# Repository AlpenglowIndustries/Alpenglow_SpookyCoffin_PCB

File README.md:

# Alpenglow_SpookyCoffin_PCB
A Halloween-themed beginning soldering blinky board with self-flickering LEDs.

You can buy this kit on Tindie or our website
https://www.tindie.com/products/alpenglow/spooky-coffin/
https://www.alpenglowindustries.com/store/p11/Spooky_Coffin.html#/

Solder instructions on Hackaday:
https://hackaday.io/project/182264-spooky-coffin

Link to the art work by Gabriel VanHelsing under a Creative Commons CC-BY-SA-3.0 license
https://commons.wikimedia.org/wiki/File:Skull_%26_Crossbones_BW.png

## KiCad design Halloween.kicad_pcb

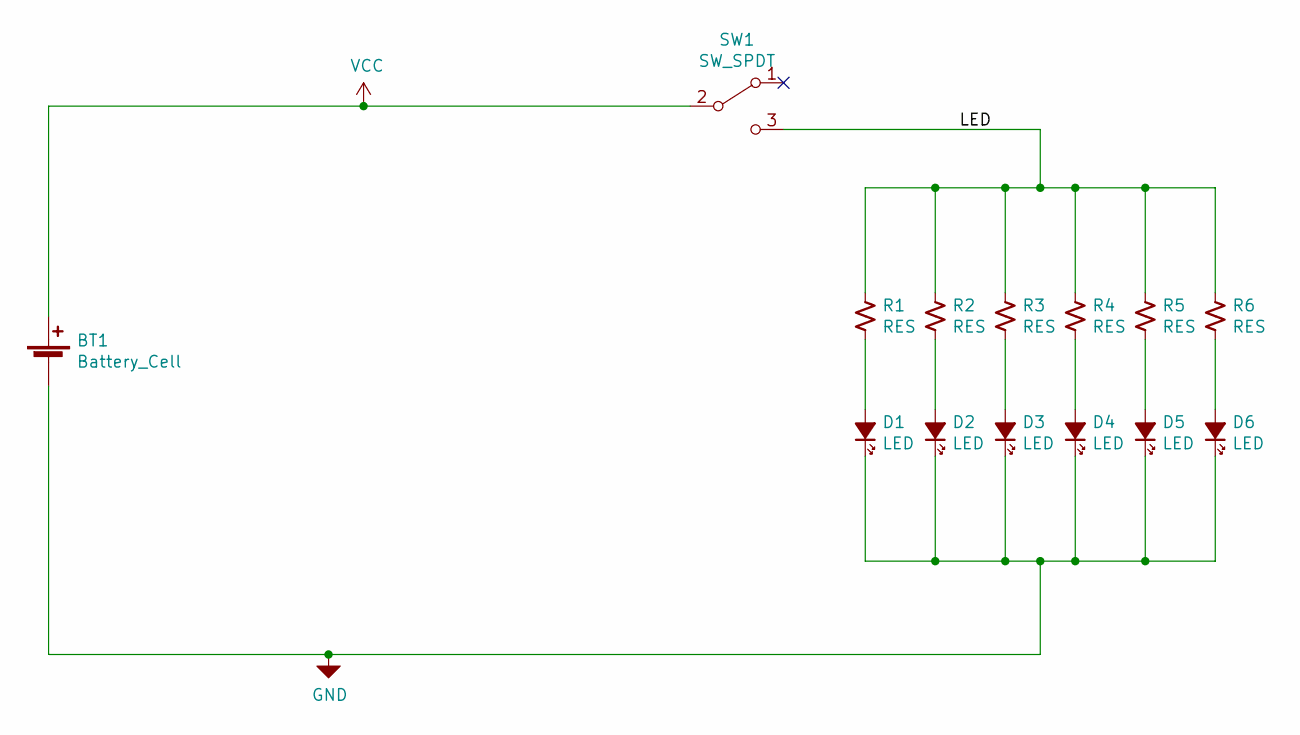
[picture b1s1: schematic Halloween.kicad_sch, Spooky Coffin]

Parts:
BT1: Battery_Cell; BatteryHolder_MPD_BK888_2032_THRU
D1, D2, D3, D4, D5, D6: LED; LED_D3.0mm
R1, R2, R3, R4, R5, R6: RES; R_Axial_DIN0207_L6.3mm_D2.5mm_P10.16mm_Horizontal
SW1: SW_SPDT; SW_SPDT_SLIDE_THRU_RTA

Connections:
/LED: R1.1, R2.1, R3.1, R4.1, R5.1, R6.1, SW1.3 (C)
GND: BT1.2 (-), D1.1 (K), D2.1 (K), D3.1 (K), D4.1 (K), D5.1 (K), D6.1 (K)
unnamed: D1.2 (A), R1.2
unnamed: D2.2 (A), R2.2
unnamed: D3.2 (A), R3.2
unnamed: D4.2 (A), R4.2
unnamed: D5.2 (A), R5.2
unnamed: D6.2 (A), R6.2
VCC: BT1.1 (+), SW1.2 (B)

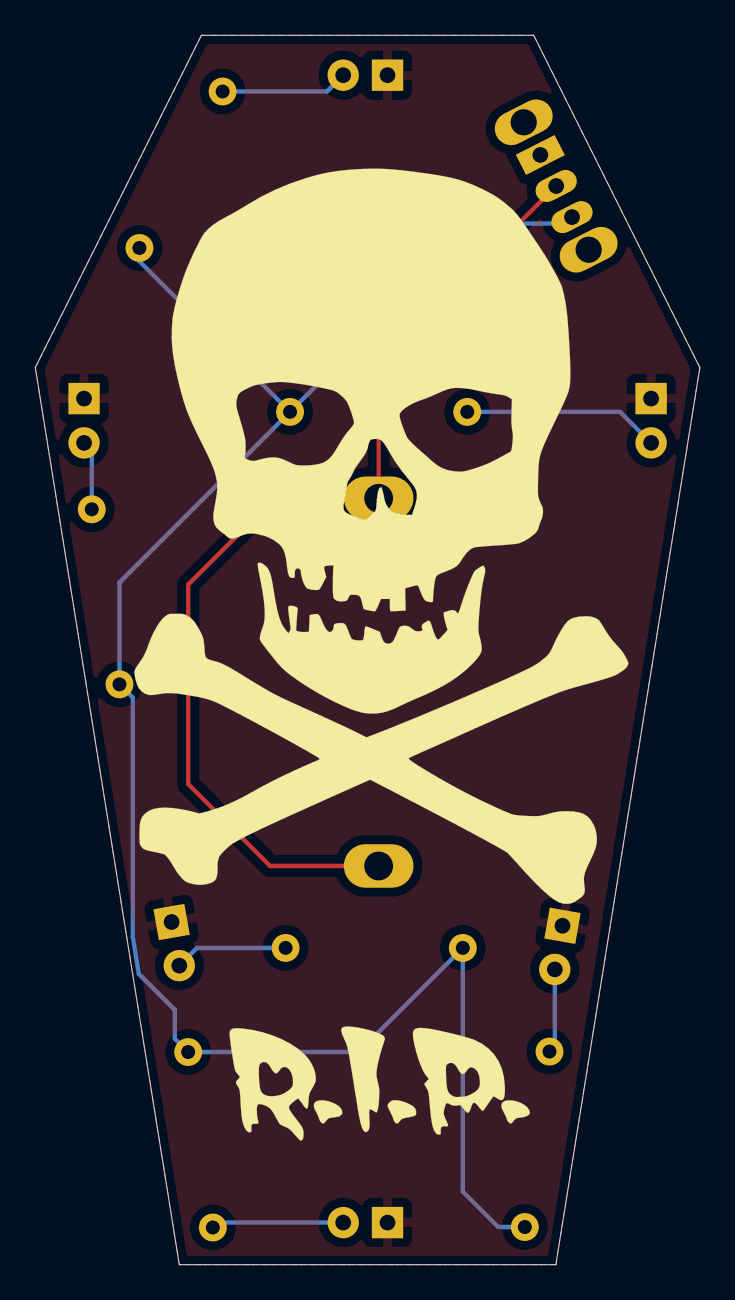
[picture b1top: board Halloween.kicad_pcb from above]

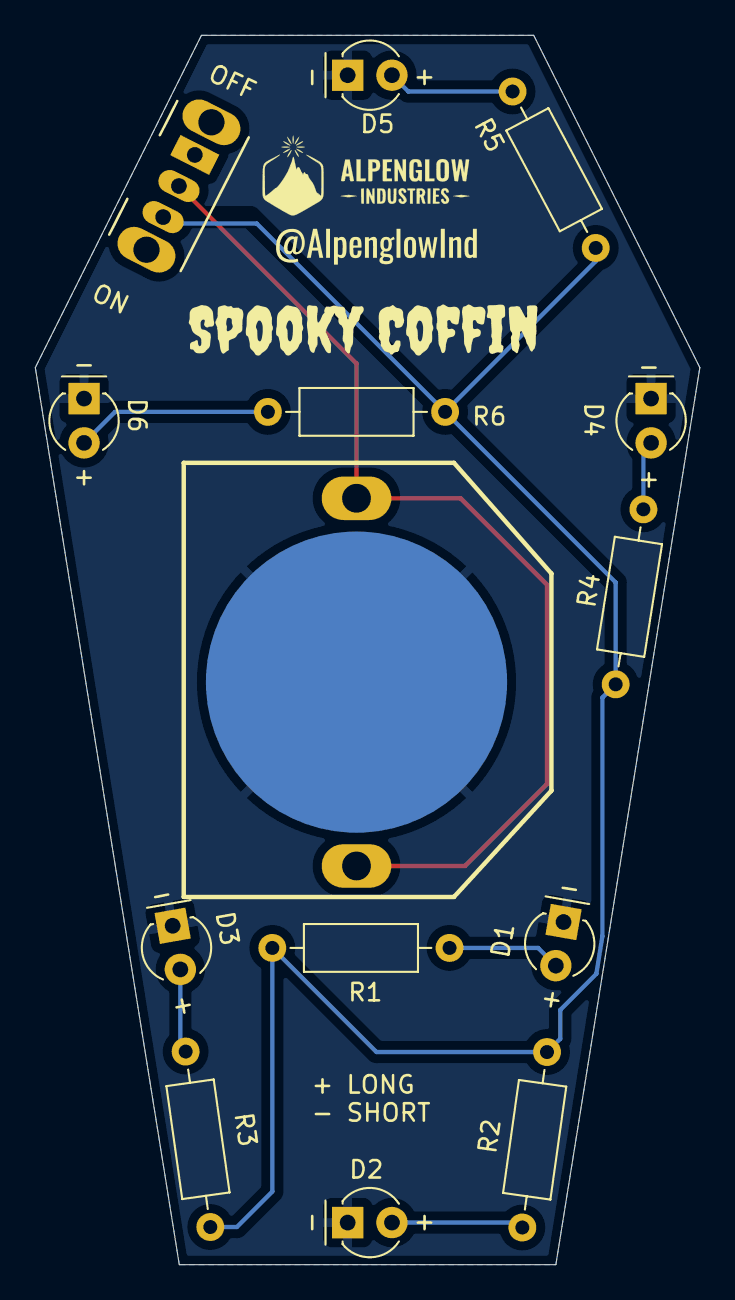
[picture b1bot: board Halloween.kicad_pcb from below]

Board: 2 copper layers, 38.1 x 70.5 mm, 14 parts (14 on the bottom side), 9 nets.

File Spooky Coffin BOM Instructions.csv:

Line,RefDes,Type,Qty Kit,Qty PCB,Description,Manufacturer,Man Part No,,,,,,,,,,,,,,,,
1,"D1, D2, D3, D4, D5, D6",LED,7,6,"Red Self Flickering, 3mm",EDGELEC, ED_YT03_FLK-R_100Pcs,,,,,,,,,,,,,,,,
2,"R1, R2, R3, R4, R5, R6",RESISTOR,7,6,220 Ohm resistor,Stackpole Electronics Inc,CF14JT220R,,,,,,,,,,,,,,,,
3,SW1,SWITCH,1,1,"Slide switch, right angle",xin cheng electronic,,,,,,,,,,,,,,,,,
4,BT1,CONN,1,1,CR2032 through-hole solder-in,PengPeng Components Store,,,,,,,,,,,,,,,,,
5,,PCB,1,1,,,,,,,,,,,,,,,,,,,
7,,BATTERY,1,0,"CR2032, individually packaged, packs of 100 or 250",,,,,,,,,,,,,,,,,,
8,,MAGNET,1,0,"10 x 3 mm rare earth, adhesive",YuLe Store,,,,,,,,,,,,,,,,,
9,,PIN,1,0,Stick-on pin,Hugesavings,B07D5THSLM,,,,,,,,,,,,,,,,
,,,,,,,,,,,,,,,,,,,,,,,
,,,,,,,,,,,,,,,,,,,,,,,
,,,,,,,,,,,,,,,,,,,,,,,
,,,,,,,,,,,,,,,,,,,,,,,
,,,,,,,,,,,,,,,,,,,,,,,
,,,,,,,,,,,,,,,,,,,,,,,
,,,,,,,,,,,,,,,,,,,,,,,
,,,,,,,,,,,,,,,,,,,,,,,
,,,,,,,,,,,,,,,,,,,,,,,
,,,,,,,,,,,,,,,,,,,,,,,
,,,,,,,,,,,,,,,,,,,,,,,
,,,,,,,,,,,,,,,,,,,,,,,
,,,,,,,,,,,,,,,,,,,,,,,
,,,,,,,,,,,,,,,,,,,,,,,
,,,,,,,,,,,,,,,,,,,,,,,
,,,,,,,,,,,,,,,,,,,,,,,
,,,,,,,,,,,,,,,,,,,,,,,
,,,,,,,,,,,,,,,,,,,,,,,
,,,,,,,,,,,,,,,,,,,,,,,
,,,,,,,,,,,,,,,,,,,,,,,
,,,,,,,,,,,,,,,,,,,,,,,
,,,,,,,,,,,,,,,,,,,,,,,
,,,,,,,,,,,,,,,,,,,,,,,
,,,,,,,,,,,,,,,,,,,,,,,
,,,,,,,,,,,,,,,,,,,,,,,
,,,,,,,,,,,,,,,,,,,,,,,
,,,,,,,,,,,,,,,,,,,,,,,
,,,,,,,,,,,,,,,,,,,,,,,
,,,,,,,,,,,,,,,,,,,,,,,
,,,,,,,,,,,,,,,,,,,,,,,
,,,,,,,,,,,,,,,,,,,,,,,
,,,,,,,,,,,,,,,,,,,,,,,
,,,,,,,,,,,,,,,,,,,,,,,
,,,,,,,,,,,,,,,,,,,,,,,
,,,,,,,,,,,,,,,,,,,,,,,
,,,,,,,,,,,,,,,,,,,,,,,
,,,,,,,,,,,,,,,,,,,,,,,
,,,,,,,,,,,,,,,,,,,,,,,
,,,,,,,,,,,,,,,,,,,,,,,
,,,,,,,,,,,,,,,,,,,,,,,
,,,,,,,,,,,,,,,,,,,,,,,
,,,,,,,,,,,,,,,,,,,,,,,
,,,,,,,,,,,,,,,,,,,,,,,
,,,,,,,,,,,,,,,,,,,,,,,
,,,,,,,,,,,,,,,,,,,,,,,
,,,,,,,,,,,,,,,,,,,,,,,
,,,,,,,,,,,,,,,,,,,,,,,
,,,,,,,,,,,,,,,,,,,,,,,
,,,,,,,,,,,,,,,,,,,,,,,
,,,,,,,,,,,,,,,,,,,,,,,
,,,,,,,,,,,,,,,,,,,,,,,
,,,,,,,,,,,,,,,,,,,,,,,
,,,,,,,,,,,,,,,,,,,,,,,
,,,,,,,,,,,,,,,,,,,,,,,
,,,,,,,,,,,,,,,,,,,,,,,
,,,,,,,,,,,,,,,,,,,,,,,
,,,,,,,,,,,,,,,,,,,,,,,
,,,,,,,,,,,,,,,,,,,,,,,
,,,,,,,,,,,,,,,,,,,,,,,
,,,,,,,,,,,,,,,,,,,,,,,
,,,,,,,,,,,,,,,,,,,,,,,
,,,,,,,,,,,,,,,,,,,,,,,
,,,,,,,,,,,,,,,,,,,,,,,
,,,,,,,,,,,,,,,,,,,,,,,
,,,,,,,,,,,,,,,,,,,,,,,
,,,,,,,,,,,,,,,,,,,,,,,
,,,,,,,,,,,,,,,,,,,,,,,
,,,,,,,,,,,,,,,,,,,,,,,
,,,,,,,,,,,,,,,,,,,,,,,
,,,,,,,,,,,,,,,,,,,,,,,
,,,,,,,,,,,,,,,,,,,,,,,
,,,,,,,,,,,,,,,,,,,,,,,

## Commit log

2021-11-01 ignoring zip files
2022-04-01 added the Spooky Coffin / Halloween artwork footprint library
2022-04-01 updated footprint library location
2022-09-15 Changed board name to font, updated logo and LED direction
2022-09-15 used oswald font for @alpenglowind
2022-09-15 updated LED long/short
2022-09-16 Updated switch footprint
2022-10-27 updated BOM, Schematic PDF, title block, moved gerbers to seperate folder
2022-10-27 Updated gitignore, changed BOM to CSV file
